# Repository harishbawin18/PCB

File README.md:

# PPG Watch PCB Design 

## Project Overview

This project presents the design and routing of a **Photoplethysmography (PPG) based wearable watch PCB**, developed using **KiCad 9.0**.
The PCB is designed to acquire pulse signals using an optical PPG sensor and support wearable health monitoring applications.
---
## Key Features
* Compact **wearable watch-size PCB layout**
* Designed using **KiCad 9.0**
* **Single-layer component placement**
* **Multi-layer routing** for optimized signal flow
* Clear **reference designators** (U1, R1, C1, etc.)
* Dedicated **power management section**
* Sensor integration for **PPG signal acquisition**
* Optimized routing for **noise reduction**
* Organized schematic hierarchy
---
## System Description
The PPG watch system includes the following major functional blocks:
### 1. PPG Sensor Module

* Optical PPG sensor detects blood volume changes.
* Uses LED light reflection technique.
* Generates analog signals corresponding to pulse rate.

### 2. Power Management Circuit

* Provides regulated voltage to all modules.
* Includes filtering capacitors for noise reduction.
* Ensures stable operation of sensor and processing units.

### 3. Processing Unit

* Microcontroller interface for signal acquisition.
* Processes raw PPG signals.
* Enables communication with external systems.

### 4. PCB Layout Design

* Compact layout suitable for wearable form factor.
* Optimized component placement for shorter routing paths.
* Ground routing designed to reduce noise interference.

---

## Design Tools Used

* **EDA Tool:** KiCad 9.0
* **PCB Design:** Schematic + Layout
* **Library Management:** Custom and standard KiCad libraries

---

## PCB Design Specifications

| Parameter           | Value                  |
| ------------------- | ---------------------- |
| PCB Tool            | KiCad 9.0              |
| Layers Used         | Multi-layer routing    |
| Component Placement | Single-layer placement |
| Design Type         | Wearable PCB           |
| Application         | Pulse Monitoring (PPG) |

---

## Files Included in Repository

* `.kicad_pro` — Project file
* `.kicad_sch` — Schematic design
* `.kicad_pcb` — PCB layout
* `.pretty` — Custom footprints
* Backup schematic references
* Supporting design files

---

## Design Considerations

The following engineering practices were followed during PCB development:

* Short routing paths to reduce signal delay
* Proper decoupling capacitor placement
* Organized power distribution
* Clear component labeling
* Noise-sensitive routing considerations
* Manufacturable PCB layout structure

---

## Applications

This PCB design can be used in:

* Wearable health monitoring devices
* Heart rate monitoring systems
* Biomedical signal acquisition systems
* Smart wearable electronics
* Embedded biomedical devices

---

## Learning Outcomes

Through this project, the following skills were developed:

* PCB schematic design
* Multi-layer PCB routing
* Component placement optimization
* Power and signal integrity considerations
* Wearable PCB design techniques
* KiCad professional workflow
* Hardware documentation practices

---

## Future Improvements

Possible future enhancements include:

* Integration with wireless communication (BLE)
* Battery charging circuit addition
* Sensor accuracy improvements
* Miniaturized PCB version
* Enclosure design for wearable deployment

---

## Author

**Harish Bawin**
Electronics and Communication Engineering (ECE)
PCB Design | Embedded Systems | Hardware Development

---

## License

This project is intended for educational and learning purposes.

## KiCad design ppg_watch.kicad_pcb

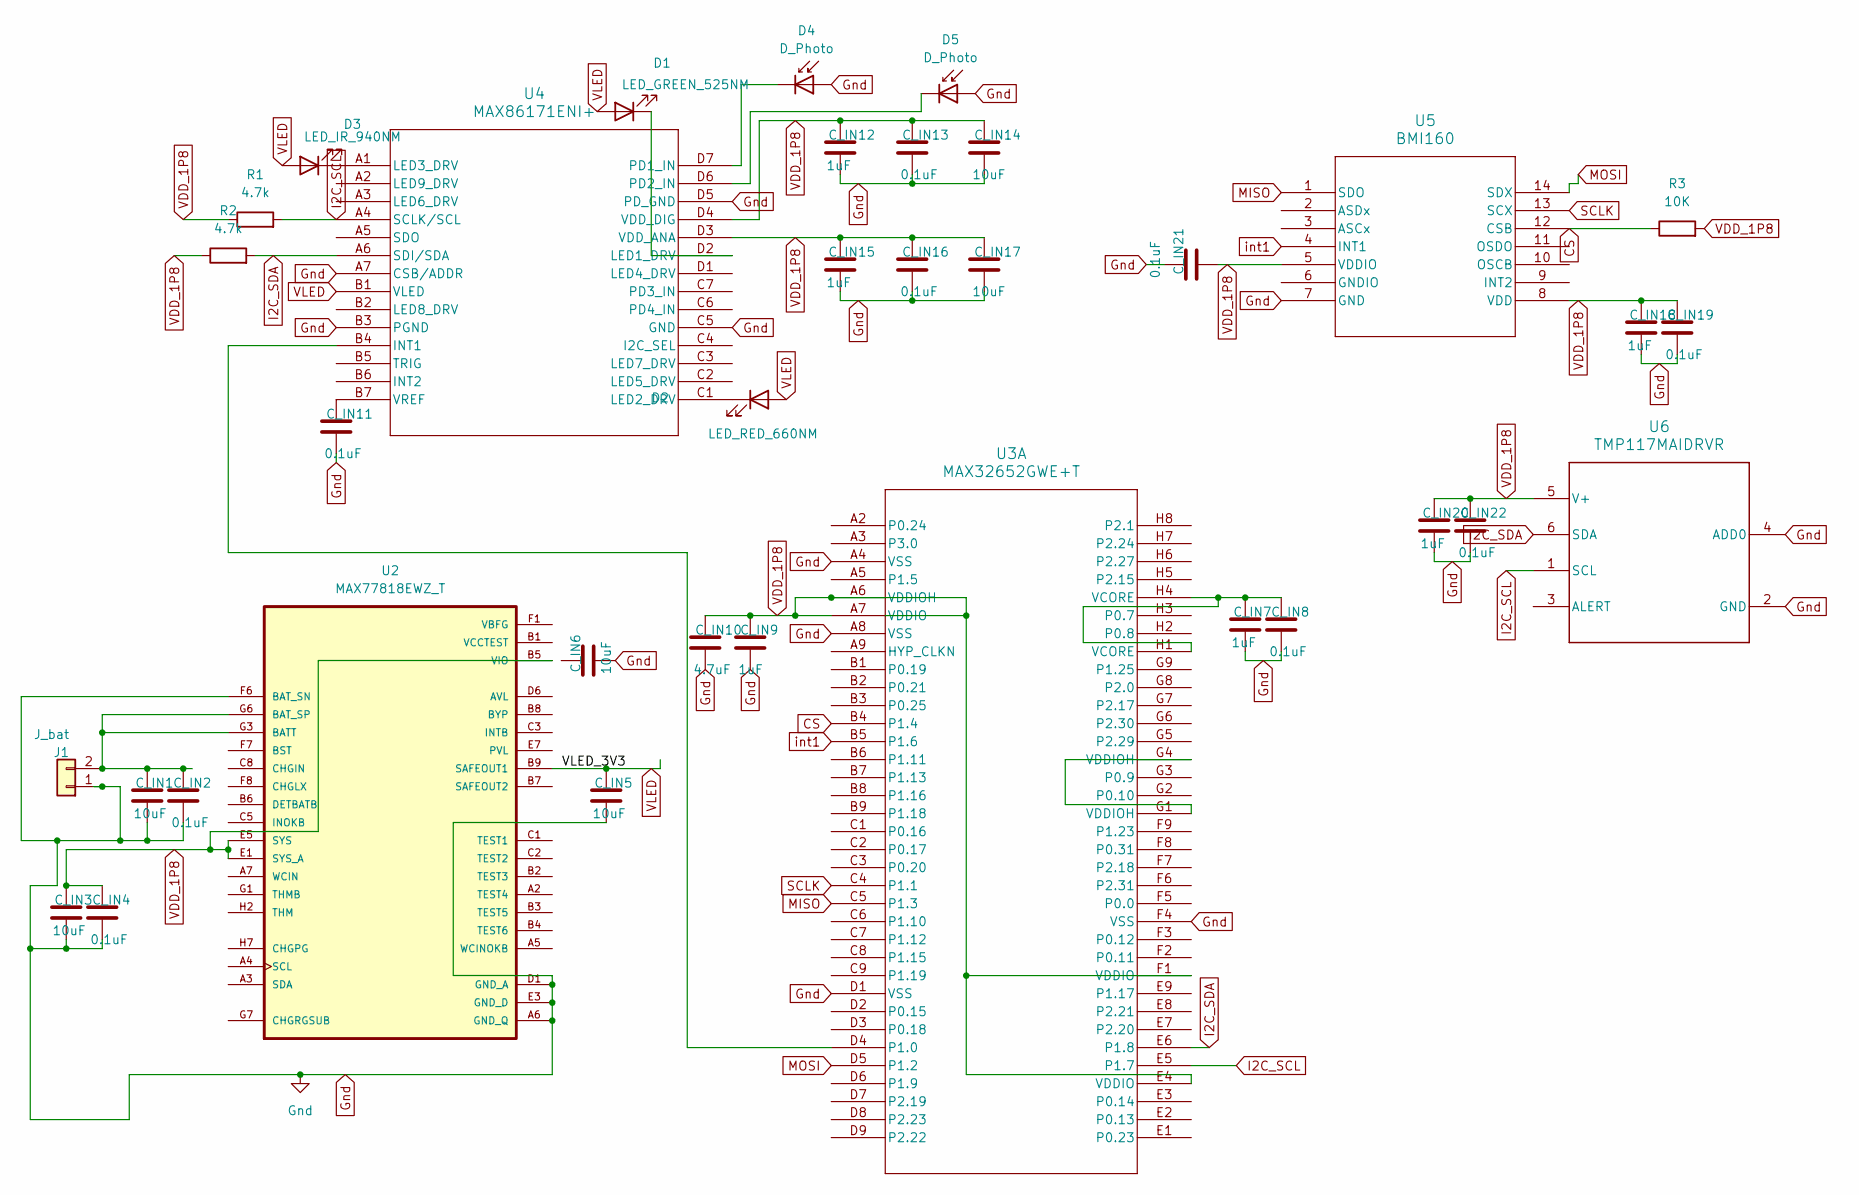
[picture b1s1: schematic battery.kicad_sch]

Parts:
C_IN1, C_IN3, C_IN5, C_IN6, C_IN14, C_IN17: 10uF; C_01005_0402Metric
C_IN2, C_IN4, C_IN8, C_IN11, C_IN13, C_IN16, C_IN19, C_IN21, C_IN22: 0.1uF; C_01005_0402Metric
C_IN7, C_IN9, C_IN12, C_IN15, C_IN18, C_IN20: 1uF; C_01005_0402Metric
C_IN10: 4.7uF; C_01005_0402Metric
D1: LED_GREEN_525NM; LED_0402_1005Metric
D2: LED_RED_660NM; LED_0402_1005Metric
D3: LED_IR_940NM; LED_0402_1005Metric
D4, D5: D_Photo; D_0603_1608Metric
J1: J_bat; JST_SH_SM02B-SRSS-TB_1x02-1MP_P1.00mm_Horizontal
R1, R2: 4.7k; R_0402_1005Metric
R3: 10K; R_0402_1005Metric
U2: MAX77818EWZ_T; BGA72N40P9X8_386X360X69N
U3: MAX32652GWE+T; 21-100219C_W1404A4&plus_1_MXM
U4: MAX86171ENI+; 21-100259_N281A2&plus_1_MXM
U5: BMI160; LGA_BMI3X2P5_BOS
U6: TMP117MAIDRVR; DRV0006B

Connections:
CS: R3.1, U3.B4 (P1.4), U5.12 (CSB)
Gnd: C_IN1.2, C_IN2.2, C_IN3.2, C_IN4.2, C_IN5.2, C_IN6.2, C_IN7.2, C_IN8.2, C_IN9.2, C_IN10.2, C_IN11.2, C_IN12.2, C_IN13.2, C_IN14.2, C_IN15.2, C_IN16.2, C_IN17.2, C_IN18.2, C_IN19.2, C_IN20.2, C_IN21.1, C_IN22.2, D4.2 (A), D5.2 (A), J1.1, U2.A6 (GND_Q), U2.D1 (GND_A), U2.D2 (GND_A), U2.D3 (GND_A), U2.D4 (GND_A), U2.D5 (GND_A), U2.E3 (GND_D), U2.F6 (BAT_SN), U3.A4 (VSS), U3.A8 (VSS), U3.D1 (VSS), U3.F4 (VSS), U4.A7 (CSB/ADDR), U4.B3 (PGND), U4.C5 (GND), U4.D5 (PD_GND), U5.7 (GND), U6.2 (GND), U6.4 (ADD0); also elsewhere on the board
I2C_SCL: R1.2, U3.E5 (P1.7), U4.A4 (SCLK/SCL), U6.1 (SCL)
I2C_SDA: R2.2, U3.E6 (P1.8), U4.A6 (SDI/SDA), U6.6 (SDA)
MISO: U3.C5 (P1.3), U5.1 (SDO)
MOSI: U3.D5 (P1.2), U5.14 (SDX)
unnamed: C_IN7.1, C_IN8.1, U3.H1 (VCORE), U3.H4 (VCORE)
unnamed: D1.1 (K), U4.D2 (LED1_DRV)
unnamed: D2.1 (K), U4.C1 (LED2_DRV)
unnamed: D3.1 (K), U4.A1 (LED3_DRV)
unnamed: D4.1 (K), U4.D7 (PD1_IN)
unnamed: D5.1 (K), U4.D6 (PD2_IN)
unnamed: C_IN1.1, C_IN2.1, J1.2, U2.G3 (BATT), U2.G4 (BATT), U2.G6 (BAT_SP), U2.H3 (BATT), U2.H4 (BATT)
unnamed: U2.B8 (BYP), U2.C7 (BYP), U2.D7 (BYP), U2.E8 (BYP), U2.E9 (BYP)
unnamed: U2.C8 (CHGIN), U2.C9 (CHGIN), U2.D8 (CHGIN), U2.D9 (CHGIN)
unnamed: U2.F8 (CHGLX), U2.F9 (CHGLX), U2.G8 (CHGLX), U2.G9 (CHGLX)
unnamed: U2.H7 (CHGPG), U2.H8 (CHGPG), U2.H9 (CHGPG)
unnamed: U2.A7 (WCIN), U2.A8 (WCIN)
unnamed: U3.D4 (P1.0), U4.B4 (INT1)
unnamed: U3.G1 (VDDIOH), U3.G4 (VDDIOH)
unnamed: C_IN11.1, U4.B7 (VREF)
SCLK: U3.C4 (P1.1), U5.13 (SCX)
VDD_1P8: C_IN3.1, C_IN4.1, C_IN9.1, C_IN10.1, C_IN12.1, C_IN13.1, C_IN14.1, C_IN15.1, C_IN16.1, C_IN17.1, C_IN18.1, C_IN19.1, C_IN20.1, C_IN21.2, C_IN22.1, R1.1, R2.1, R3.2, U2.B5 (VIO), U2.E1 (SYS_A), U2.E5 (SYS), U2.F2 (SYS_A), U2.F5 (SYS), U2.G5 (SYS), U2.H5 (SYS), U2.H6 (SYS), U3.A6 (VDDIOH), U3.A7 (VDDIO), U3.E4 (VDDIO), U3.F1 (VDDIO), U4.D3 (VDD_ANA), U4.D4 (VDD_DIG), U5.5 (VDDIO), U5.8 (VDD), U6.5 (V+); also elsewhere on the board
VLED: C_IN5.1, D1.2 (A), D2.2 (A), D3.2 (A), U2.B9 (SAFEOUT1), U4.B1 (VLED)
int1: U3.B5 (P1.6), U5.4 (INT1)

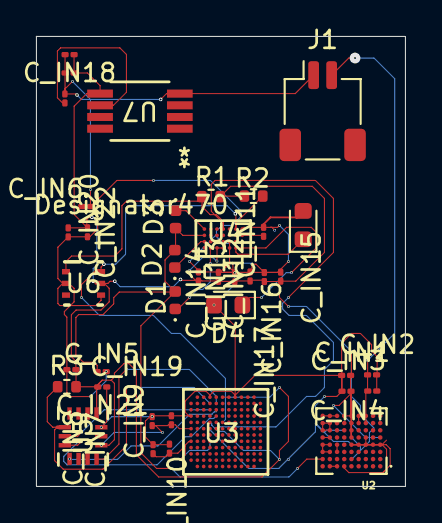
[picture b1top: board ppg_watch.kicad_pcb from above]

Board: 2 copper layers, 20.5 x 25.0 mm, 39 parts (0 on the bottom side), 26 nets.

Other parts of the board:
C_IN23, C_IN24: 0.1uF; C_01005_0402Metric
U7: AD8237ARMZ; RM_8_ADI

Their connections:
Gnd: C_IN23.2, C_IN24.2, U7.4 (-VS); also elsewhere on the board
unnamed: C_IN24.1, U7.6 (REF)
VDD_1P8: C_IN23.1, U7.5 (+VS); also elsewhere on the board

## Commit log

2026-04-24 Added PPG Watch PCB files
2026-04-24 Add README.md for PPG Watch PCB Design project
    Added detailed project overview, features, system description, design tools, specifications, applications, learning outcomes, future improvements, author information, and license.
